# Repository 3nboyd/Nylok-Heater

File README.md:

# Nylok Handheld Induction Heater Controller

A two-mode handheld induction-heater controller designed in KiCad for the Notre Dame / Marmon / Nylok Innovate-a-thon.

## Heater product design

The image above shows the actual heater product design.

**Interested in the CAD files and final product designs? Please contact [Noah Boyd](https://github.com/3nboyd).**

## Full cost analysis

**[Read the complete breakdown, calculations, and cost analysis](COST_ANALYSIS.md)** · [Download the original Word document](Nylok_Heater_Cost_Analysis.docx) · [View the source on Google Drive](https://docs.google.com/document/d/1d1SXaH8sqosNrCxIEX-nSozUCm1gSHQc/edit)

The full analysis covers the itemized prototype parts, two-mode controller and display, heating calculations, battery runtime, and estimated manufacturing costs at a 5,000-unit order quantity.

| Cost scenario | Basic heater | Two-mode heater with countdown |
|---|---:|---:|
| Prototype parts allocation | $18.06 | $31.37 |
| Estimated manufacturing cost per heater at 5,000 units | $13.14 | $19.14 |

Source prices were checked October 3, 2026. Prototype figures exclude the housing, tools, shipping, and tax; production figures include estimated housing, assembly, functional test, packaging, and reserve. See the full analysis for all assumptions and exclusions.

## Controller PCB

> [!CAUTION]
> **Do not fabricate or energize this board without a qualified electrical and safety review.** Review the power stage, battery protection, thermal behavior, and coil compatibility before use.

## Overview

The controller uses two protected 18650 cells in series to power a controller board that:

- measures input current;
- provides regulated 5 V and 3.3 V rails;
- controls a switched DC output for an **external zero-voltage-switching (ZVS) induction driver**;
- exposes an Inter-Integrated Circuit (I2C) display connector; and
- provides a Serial Wire Debug (SWD) programming header for the STM32 controller.

The work coil connects to the external ZVS driver, not directly to connector J2 or the battery.

## Repository contents

```text
.
├── hardware/   KiCad project, schematic, PCB, bill of materials (BOM), and logical net map
├── COST_ANALYSIS.md                 Full readable cost analysis and calculations
├── Nylok_Heater_Cost_Analysis.docx   Original complete cost-analysis document
├── docs/       Engineering study and connection diagram
├── fab/        Fabrication and electrical-review notes
├── renders/    Heater product design and board views
└── scripts/    Repository package checks
```

Key files:

- [`COST_ANALYSIS.md`](COST_ANALYSIS.md): full cost breakdown, calculations, production estimates, and references
- [`Nylok_Heater_Cost_Analysis.docx`](Nylok_Heater_Cost_Analysis.docx): original analysis document
- [`renders/Nylok_Heater_Product_Design.png`](renders/Nylok_Heater_Product_Design.png): actual heater product design rendering
- [`hardware/Nylok_Heater.kicad_pro`](hardware/Nylok_Heater.kicad_pro): KiCad project
- [`hardware/Nylok_Heater.sch`](hardware/Nylok_Heater.sch): legacy KiCad schematic
- [`hardware/Nylok_Heater.kicad_pcb`](hardware/Nylok_Heater.kicad_pcb): nominal 38 mm × 100 mm, two-layer PCB
- [`hardware/BOM.csv`](hardware/BOM.csv): component/value list
- [`hardware/NETS.csv`](hardware/NETS.csv): logical net map
- [`docs/Nylok_Labeled_PCB_and_Connections.png`](docs/Nylok_Labeled_PCB_and_Connections.png): labeled placement and connection diagram
- [`docs/Induction_System_Specification.md`](docs/Induction_System_Specification.md): research, assumptions, calculations, and primary sources

## Open the project

1. Install KiCad 10 or later.
2. Clone the repository:

   ```bash
   git clone https://github.com/3nboyd/Nylok-Heater.git
   cd Nylok-Heater
   ```

3. Open `hardware/Nylok_Heater.kicad_pro`.
4. Allow KiCad to convert the legacy `.sch` file if prompted, but review the resulting diff before committing it.
5. Read [`docs/Induction_System_Specification.md`](docs/Induction_System_Specification.md) before using the design data.

To check the repository package itself:

```bash
python3 scripts/validate_repo.py
```

This script checks file presence, project metadata, BOM/net structure, PCB references, and PNG integrity. It does **not** certify electrical correctness, safety, or fabrication readiness.

## Safety

Induction heating combines high current, resonant switching, strong local heating, rechargeable cells, and potentially hazardous workpiece temperatures. A short circuit, unsuitable component, control fault, inadequate insulation, or incorrect battery protection can cause burns, fire, cell venting, or equipment damage.

Do not build or energize the heater until a qualified engineer has reviewed the power stage, protection, thermal behavior, creepage/clearance, component ratings, coil/tank behavior, enclosure, battery system, and failure modes. Use current-limited isolated laboratory power during early development and appropriate PPE, guarding, instrumentation, and fire precautions.

## Contributing

Improvements are welcome. Please read [`CONTRIBUTING.md`](CONTRIBUTING.md) before opening an issue or pull request. Do not mark the design fabrication-ready without appropriate engineering review and test evidence.

## License

No open-source license has been selected. The repository is public for review and collaboration, but publication alone does not grant permission to copy, modify, manufacture, or redistribute the design. The owner can add an OSI/OSHWA-compatible license later after choosing the intended terms.

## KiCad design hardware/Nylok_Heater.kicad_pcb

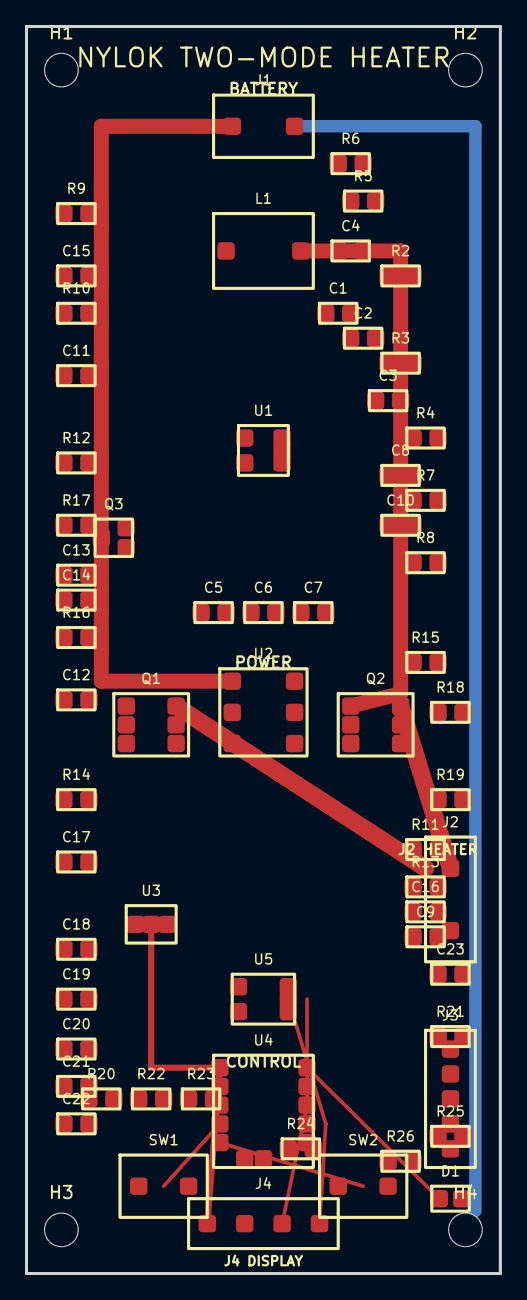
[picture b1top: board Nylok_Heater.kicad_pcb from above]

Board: 2 copper layers, 38.0 x 100.0 mm, 68 parts (0 on the bottom side), 20 nets.

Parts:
C1: 10n; C1
C2: 100n; C2
C3: 100n; C3
C4: 10n; C4
C5: 22u 25V X7R; C5
C6: 22u 25V X7R; C6
C7: 22u 25V X7R; C7
C8: 100n; C8
C9: 1u; C9
C10: 100n; C10
C11: 47n; C11
C12: 47u 10V X7R; C12
C13: 47u 10V X7R; C13
C14: 47u 10V X7R; C14
C15: 56p C0G; C15
C16: 10n; C16
C17: 1u 16V; C17
C18: 2.2u; C18
C19: 10u; C19
C20: 100n; C20
C21: 4.7u; C21
C22: 100n; C22
C23: 100n; C23
D1: STATUS; D1
H1, H2, H3, H4: M2.5; MountingHole_2.5mm
J1: BATTERY IN; J1
J2: HEATER OUT; J2
J3: SWD; J3
J4: I2C DISPLAY; J4
L1: 1.5uH; L1
Q1: AO4409; Q1
Q2: AO4409; Q2
Q3: BC817-40; Q3
R2: 10; R2
R3: 10; R3
R4: 1k; R4
R5: 100k; R5
R6: 33k; R6
R7: 100k; R7
R8: 10k; R8
R9: 23.2k 1%; R9
R10: 2.49k 1%; R10
R11: 1k; R11
R12: 54.9k 1%; R12
R13: 4.7k; R13
R14: 100; R14
R15: 47k; R15
R16: 4.7k; R16
R17: 100k; R17
R18: 100k; R18
R19: 47k; R19
R20: 10k; R20
R21: 100k; R21
R22: 4.7k; R22
R23: 4.7k; R23
R24: 10k; R24
R25: 10k; R25
R26: 1k; R26
SW1: START/STOP; SW1
SW2: MODE; SW2
U1: INA180A2; U1
U2: MP8771; U2
U3: AP7381-33; U3
U4: STM32G030F6P6; U4
U5: MCP4725; U5

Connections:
BAT_RAW: J1.1, R5.1, R6.1, R9.1, U2.1
BUCK_SW: L1.1, U2.4
DAC_OUT: C16.1, C17.1, R11.1, R13.1, U2.3, U5.5
GATE: Q1.1, Q2.1, Q3.2, R14.2, R15.1, R18.1
GND: C1.2, C2.2, C3.2, C4.2, C5.2, C6.2, C7.2, C8.2, C9.2, C10.2, C11.2, C12.2, C13.2, C14.2, C15.2, C16.2, C17.2, C18.2, C19.2, C20.2, C21.2, C22.2, C23.2, D1.2, J1.2, J2.2, J3.5, J4.1, Q3.3, R2.2, R3.2, R4.2, R5.2, R7.2, R8.2, R9.2, R10.2, R11.2, R12.2, R13.2, R16.2, R17.2, R18.2, R19.2, R24.2, R26.2, SW1.2, SW2.2, U1.2, U2.2, U2.6, U3.1, U4.2, U5.2
HEATER_EN: Q3.1, R14.1, R16.1, R19.1, U4.7
HEATER_PLUS: J2.1, Q1.4, Q1.5, Q1.6, Q2.4, Q2.5, Q2.6
ISENSE: C11.1, C15.1, R4.1, R6.2, R10.1, U1.1, U4.3
NRST: J3.3, R23.1, R24.1, U4.12
SCL: J4.3, R20.1, U4.8, U5.3
SDA: J4.4, R22.1, U4.9, U5.4
SENSE_N: R2.1, U1.3
SENSE_P: R3.1, U1.4
STATUS: D1.1, R26.1, U4.6
SWCLK: J3.2, R25.1, U4.11
SWDIO: J3.1, R21.1, U4.10
SW_MODE: SW2.1, U4.5
SW_START: SW1.1, U4.4
V3V3: C1.1, C2.1, C3.1, C4.1, C8.1, C9.1, C10.1, C18.1, C19.1, C20.1, C21.1, C22.1, C23.1, J3.4, J4.2, R12.1, R17.1, R20.2, R21.2, R22.2, R23.2, R25.2, U1.5, U3.2, U4.1, U5.1
V5: C5.1, C6.1, C7.1, C12.1, C13.1, C14.1, L1.2, Q1.2, Q1.3, Q2.2, Q2.3, R7.1, R8.1, R15.2, U2.5, U3.3

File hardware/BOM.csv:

Reference,Symbol/MPN,Value,Footprint,Function
J1,Conn_01x02,PROTECTED BATTERY INPUT,Connector_Generic:Conn_01x02,2-pin high-current input
J2,Conn_01x02,HEATER POWER OUTPUT,Connector_Generic:Conn_01x02,To external ZVS driver DC input
J3,Conn_01x05,SWD PROGRAMMING,Connector_Generic:Conn_01x05,SWDIO/SWCLK/NRST/3V3/GND
J4,Conn_01x04,I2C DISPLAY,Connector_Generic:Conn_01x04,GND/3V3/SCL/SDA
U1,INA180A2IDBVR,INA180A2,Package_TO_SOT_SMD:SOT-23-5,Current sense amplifier
U2,MP8771GQ-Z,MP8771,Package_DFN_QFN:QFN-16-1EP_3x3mm_P0.5mm_EP1.7x1.7mm,Buck regulator
U3,AP7381-33Y-13,AP7381-33,Package_TO_SOT_SMD:SOT-89-3,3.3 V regulator
U4,STM32G030F6P6,STM32G030F6P6,Package_SO:TSSOP-20_4.4x6.5mm_P0.65mm,MCU / timer / controller
U5,MCP4725A0T-E/CH,MCP4725,Package_TO_SOT_SMD:SOT-23-6,Power-setting DAC
Q1,AO4409,AO4409,Package_SO:SO-8_3.9x4.9mm_P1.27mm,Heater high-side switch
Q2,AO4409,AO4409,Package_SO:SO-8_3.9x4.9mm_P1.27mm,Heater high-side switch
Q3,BC817-40,BC817-40,Package_TO_SOT_SMD:SOT-23,Gate driver transistor
L1,SRP1265A-1R5M,1.5uH,Inductor_SMD:L_12.5x12.5_H6.5,Buck inductor
D1,LED,STATUS,LED_SMD:LED_0603_1608Metric,Status LED
SW1,SW_Push,START / STOP,Button_Switch_SMD:SW_SPST_TL3301AN,Start/stop button
SW2,SW_Push,LIQUID / POWDER,Button_Switch_SMD:SW_SPST_TL3301AN,Mode button
R1,R,5m 2W 1%,Resistor_SMD:R_2512_6332Metric,
R2,R,10,Resistor_SMD:R_0603_1608Metric,
R3,R,10,Resistor_SMD:R_0603_1608Metric,
R4,R,1k,Resistor_SMD:R_0603_1608Metric,
R5,R,100k,Resistor_SMD:R_0603_1608Metric,
R6,R,33k,Resistor_SMD:R_0603_1608Metric,
R7,R,100k,Resistor_SMD:R_0603_1608Metric,
R8,R,10k,Resistor_SMD:R_0603_1608Metric,
R9,R,23.2k 1%,Resistor_SMD:R_0603_1608Metric,
R10,R,2.49k 1%,Resistor_SMD:R_0603_1608Metric,
R11,R,1k,Resistor_SMD:R_0603_1608Metric,
R12,R,54.9k 1%,Resistor_SMD:R_0603_1608Metric,
R13,R,4.7k,Resistor_SMD:R_0603_1608Metric,
R14,R,100,Resistor_SMD:R_0603_1608Metric,
R15,R,47k,Resistor_SMD:R_0603_1608Metric,
R16,R,4.7k,Resistor_SMD:R_0603_1608Metric,
R17,R,100k,Resistor_SMD:R_0603_1608Metric,
R18,R,100k,Resistor_SMD:R_0603_1608Metric,
R19,R,47k,Resistor_SMD:R_0603_1608Metric,
R20,R,10k,Resistor_SMD:R_0603_1608Metric,
R21,R,100k,Resistor_SMD:R_0603_1608Metric,
R22,R,4.7k,Resistor_SMD:R_0603_1608Metric,
R23,R,4.7k,Resistor_SMD:R_0603_1608Metric,
R24,R,10k,Resistor_SMD:R_0603_1608Metric,
R25,R,10k,Resistor_SMD:R_0603_1608Metric,
R26,R,1k,Resistor_SMD:R_0603_1608Metric,
C1,C,10n,Capacitor_SMD:C_0603_1608Metric,
C2,C,100n,Capacitor_SMD:C_0603_1608Metric,
C3,C,100n,Capacitor_SMD:C_0603_1608Metric,
C4,C,10n,Capacitor_SMD:C_0603_1608Metric,
C5,C,22u 25V X7R,Capacitor_SMD:C_1210_3225Metric,
C6,C,22u 25V X7R,Capacitor_SMD:C_1210_3225Metric,
C7,C,22u 25V X7R,Capacitor_SMD:C_1210_3225Metric,
C8,C,100n,Capacitor_SMD:C_0603_1608Metric,
C9,C,1u,Capacitor_SMD:C_0603_1608Metric,
C10,C,100n,Capacitor_SMD:C_0603_1608Metric,
C11,C,47n,Capacitor_SMD:C_0603_1608Metric,
C12,C,47u 10V X7R,Capacitor_SMD:C_1210_3225Metric,
C13,C,47u 10V X7R,Capacitor_SMD:C_1210_3225Metric,
C14,C,47u 10V X7R,Capacitor_SMD:C_1210_3225Metric,
C15,C,56p C0G,Capacitor_SMD:C_0603_1608Metric,
C16,C,10n,Capacitor_SMD:C_0603_1608Metric,
C17,C,1u 16V,Capacitor_SMD:C_0603_1608Metric,
C18,C,2.2u,Capacitor_SMD:C_0603_1608Metric,
C19,C,10u,Capacitor_SMD:C_0603_1608Metric,
C20,C,100n,Capacitor_SMD:C_0603_1608Metric,
C21,C,4.7u,Capacitor_SMD:C_0603_1608Metric,
C22,C,100n,Capacitor_SMD:C_0603_1608Metric,
C23,C,100n,Capacitor_SMD:C_0603_1608Metric,
